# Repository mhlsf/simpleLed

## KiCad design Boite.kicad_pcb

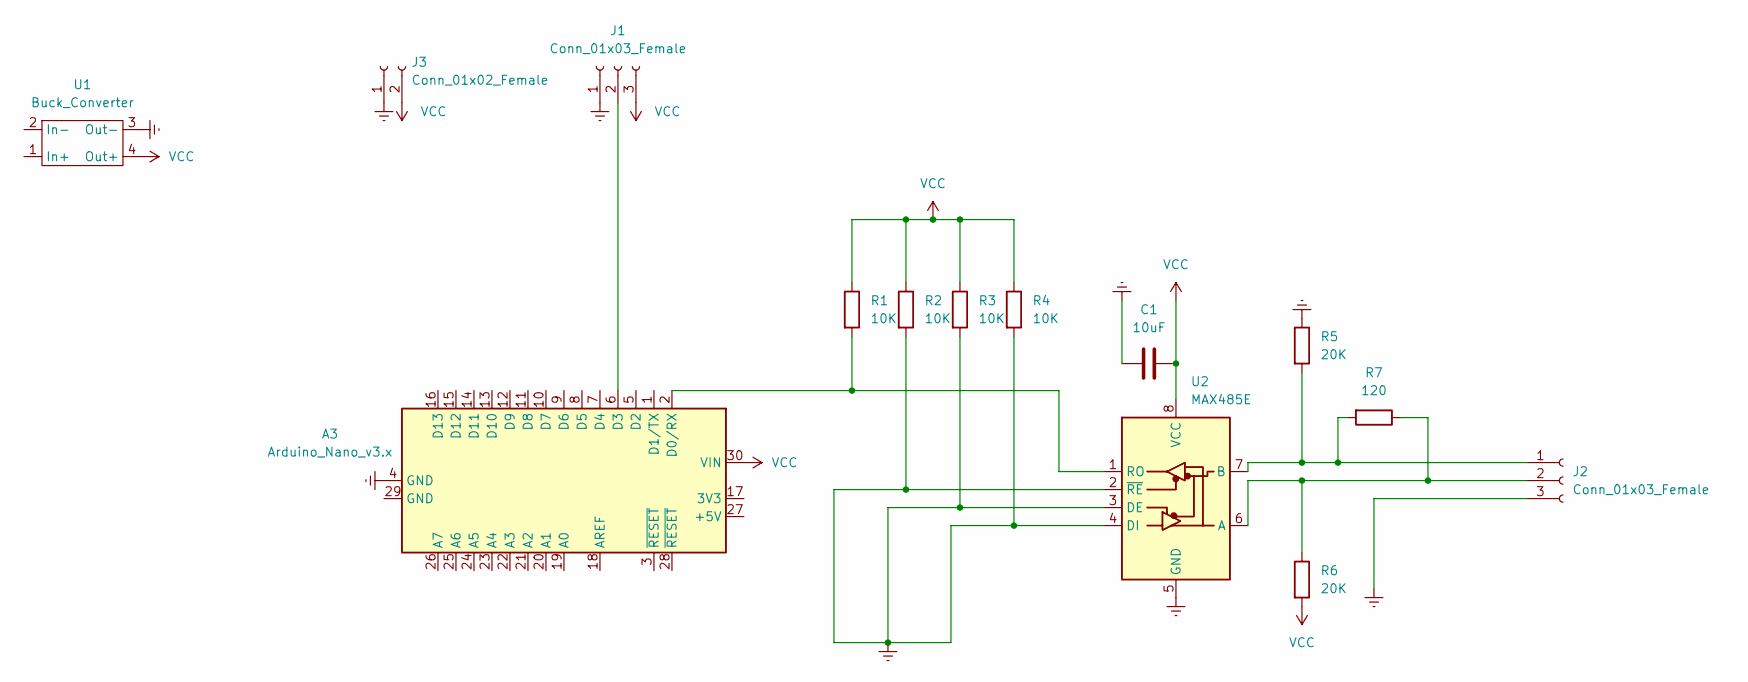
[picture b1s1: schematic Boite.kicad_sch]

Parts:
A3: Arduino_Nano_v3.x; Arduino_Nano
C1: 10uF; C_0603_1608Metric
J1, J2: Conn_01x03_Female; PinHeader_1x03_P1.27mm_Vertical
J3: Conn_01x02_Female; PinHeader_1x02_P1.27mm_Vertical
R1, R2, R3, R4: 10K; R_0603_1608Metric
R5, R6: 20K; R_0603_1608Metric
R7: 120; R_0603_1608Metric
U1: Buck_Converter
U2: MAX485E; SOIC-8-1EP_3.9x4.9mm_P1.27mm_EP2.29x3mm

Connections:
Earth: A3.4 (GND), C1.1, J1.1, J2.3, J3.1, R2.2, R3.2, R4.2, R5.1, U1.3 (Out-), U2.2 (~RE), U2.3 (DE), U2.4 (DI), U2.5 (GND)
unnamed: A3.2 (D0/RX), R1.2, U2.1 (RO)
unnamed: A3.6 (D3), J1.2
unnamed: J2.1, R5.2, R7.2, U2.7 (B)
unnamed: J2.2, R6.1, R7.1, U2.6 (A)
VCC: A3.30 (VIN), C1.2, J1.3, J3.2, R1.1, R2.1, R3.1, R4.1, R6.2, U1.4 (Out+), U2.8 (VCC)

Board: 2 copper layers, 13 parts (1 on the bottom side), 6 nets, no tracks yet.
